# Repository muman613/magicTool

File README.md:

# magicTool

`magicTool` is a Raspberry Pi Pico 2 / Pico 2 W helper project used to drive debug GPIO over a simple USB serial command interface. It is intended as a standalone debug aid for other hardware and firmware work, including Argus-related debugging, but it is not part of the Argus project itself.

## Hardware Versions

The firmware supports two magicTool hardware version values:

- Hardware v1 is the basic configuration. It provides the USB serial command interface, D0-D3 GPIO outputs, and D0-D1 GPIO inputs without the display stack.
- Hardware v2 adds support for a 128x128 LCD display. Display-enabled builds compile the ST7735 driver, LVGL UI, and display task so the onboard screen can mirror the D0-D3 output states.

Select the target hardware with `MAGICTOOL_HW_VERSION`: use `1` for hardware v1 and `2` for hardware v2.

## Repository Layout

This repository is organized so the current Pico firmware lives in its own subdirectory and the project can grow without mixing host-side code, hardware assets, and embedded firmware sources.

```text
magicTool/
├── CMakeLists.txt
├── CMakePresets.json
├── docs/
│   ├── magiclib.md
│   ├── pico2w-build.md
│   └── pinout references
├── README.md
├── build.sh
├── firmware/
│   ├── CMakeLists.txt
│   ├── include/
│   ├── main.cpp
│   ├── src/
│   ├── reset_interface.c
│   ├── tusb_config.h
│   └── usb_descriptors.c
├── hardware/
│   ├── README.md
│   ├── generate_magictool_kicad.py
│   └── magictool.kicad_*
├── host/
│   ├── CMakeLists.txt
│   ├── README.md
│   ├── examples/
│   ├── include/
│   ├── src/
│   └── *.pc.in
├── resources/
│   ├── icons/
│   └── launchers/
├── magicTool_firmware.code-workspace
└── magicTool_host.code-workspace
```

- `firmware/` contains the Pico SDK and FreeRTOS based firmware build, plus optional LVGL display support for hardware v2.
- `host/` contains native POSIX and Qt5 libraries for talking to the Pico CDC serial device.
- `hardware/` contains the generated KiCad carrier board project and the script used to regenerate it.
- `docs/` contains project documentation, build notes, pinout references, and host library usage examples.
- `resources/` contains desktop integration assets for the host UI.

## Requirements

- `cmake` 3.16 or newer
- a native build tool supported by CMake such as `make` or `ninja`
- A working Raspberry Pi Pico SDK checkout
- `PICO_SDK_PATH` exported in your shell environment
- FreeRTOS-Kernel is fetched automatically for firmware builds when `FREERTOS_KERNEL_PATH` is not set
- Optionally, a Raspberry Pi FreeRTOS-Kernel checkout with `FREERTOS_KERNEL_PATH` exported in your shell environment, or a checkout at `/home/michael/gitroot/pico-dev/FreeRTOS-Kernel`
- An ARM embedded toolchain compatible with the Pico SDK
- LVGL is required only when building display-enabled firmware for hardware v2, which means `MAGICTOOL_HW_VERSION=2`. Set `LVGL_PATH` to a local checkout, clone LVGL under `firmware/external/lvgl`, or leave `MAGICTOOL_FETCH_LVGL=ON` to fetch it during configure.
- Qt5 Core and Qt5 SerialPort development packages for the Qt5 host library
- Qt5 Widgets development packages for the `magicUI` host application

The firmware presets require `PICO_SDK_PATH`. FreeRTOS-Kernel is fetched automatically unless `FREERTOS_KERNEL_PATH` points to an existing checkout:

```bash
export PICO_SDK_PATH=/path/to/pico-sdk
# Optional:
export FREERTOS_KERNEL_PATH=/path/to/FreeRTOS-Kernel
```

The host-only presets do not require the Pico SDK or FreeRTOS.

## Build

Prefer the CMake presets below. They keep host and firmware outputs in separate
build directories and avoid mixing the host toolchain with the Pico cross-toolchain.

For a concise Pico 2 W build matrix covering hardware v1 and v2, see
[docs/pico2w-build.md](docs/pico2w-build.md).

For the common cases, use the helper script:

```bash
./build.sh [pico2|pico2w] [host|fw|all] [1|2] [debug|release]
```

All arguments are optional. The defaults are `pico2`, `all`, hardware version
`1`, and `debug`:

```bash
./build.sh
```

Examples:

```bash
./build.sh pico2w fw 2 release
./build.sh pico2 host 1 debug
```

### Host Applications

The host build produces:

- `magictool`, the command-line example from `host/examples/basic_usage.cpp`
- `magictool_native`, the native command-line example from `host/examples/basic_usage_native.cpp`
- `magicUI`, the Qt Widgets application
- `libmagictool_native.a`, the native POSIX host library
- `libmagictool_qt5.a`, the Qt5 host library

Build host Debug:

```bash
cmake --preset host-debug
cmake --build --preset host-debug
```

Build host Release:

```bash
cmake --preset host-release
cmake --build --preset host-release
```

Build the native POSIX host library and `magictool_native` without Qt:

```bash
cmake -S host -B build/host-native-only \
  -DDEBUG_TOOL_BUILD_QT5=OFF \
  -DDEBUG_TOOL_BUILD_NATIVE=ON \
  -DDEBUG_TOOL_NATIVE_BUILD_EXAMPLES=ON
cmake --build build/host-native-only
```

Host output paths:

```text
build/host-debug/host/magictool
build/host-debug/host/magictool_native
build/host-debug/host/magicUI
build/host-debug/host/libmagictool_native.a
build/host-debug/host/libmagictool_qt5.a
build/host-release/host/magictool
build/host-release/host/magictool_native
build/host-release/host/magicUI
build/host-release/host/libmagictool_native.a
build/host-release/host/libmagictool_qt5.a
```

### Firmware Only

The default firmware hardware version is `MAGICTOOL_HW_VERSION=1`, which targets hardware v1 and builds the FreeRTOS USB/GPIO firmware without the display stack. Set `MAGICTOOL_HW_VERSION=2` to target hardware v2 and enable 128x128 ST7735/LVGL display support.

Build Pico 2 Debug:

```bash
cmake --preset firmware-pico2-debug
cmake --build --preset firmware-pico2-debug
```

Build Pico 2 Release:

```bash
cmake --preset firmware-pico2-release
cmake --build --preset firmware-pico2-release
```

Build Pico 2 W Debug:

```bash
cmake --preset firmware-pico2w-debug
cmake --build --preset firmware-pico2w-debug
```

Build Pico 2 W Release:

```bash
cmake --preset firmware-pico2w-release
cmake --build --preset firmware-pico2w-release
```

Firmware UF2 output paths:

```text
build/firmware-pico2-debug/firmware/magictool_fw_pico2.uf2
build/firmware-pico2-release/firmware/magictool_fw_pico2.uf2
build/firmware-pico2w-debug/firmware/magictool_fw_pico2_w.uf2
build/firmware-pico2w-release/firmware/magictool_fw_pico2_w.uf2
```

Build a display-enabled Pico 2 firmware manually by selecting hardware v2 and providing LVGL if you do not want CMake to fetch it:

```bash
cmake -S . -B build/firmware-pico2-hw2-release \
  -DCMAKE_BUILD_TYPE=Release \
  -DDEBUG_TOOL_BUILD_FIRMWARE=ON \
  -DDEBUG_TOOL_BUILD_HOST=OFF \
  -DMAGICTOOL_HW_VERSION=2 \
  -DLVGL_PATH=/path/to/lvgl
cmake --build build/firmware-pico2-hw2-release
```

### Host And Firmware Together

The combined presets build the selected firmware target and the host
applications in separate sub-builds under one top-level build directory.

Build all targets for Pico 2 Debug:

```bash
cmake --preset all-pico2-debug
cmake --build --preset all-pico2-debug
```

Build all targets for Pico 2 Release:

```bash
cmake --preset all-pico2-release
cmake --build --preset all-pico2-release
```

Build all targets for Pico 2 W Debug:

```bash
cmake --preset all-pico2w-debug
cmake --build --preset all-pico2w-debug
```

Build all targets for Pico 2 W Release:

```bash
cmake --preset all-pico2w-release
cmake --build --preset all-pico2w-release
```

Combined build output paths use nested sub-build directories:

```text
build/all-pico2-release/firmware/magictool_fw_pico2.uf2
build/all-pico2-release/host/magictool
build/all-pico2-release/host/magictool_native
build/all-pico2-release/host/magicUI
build/all-pico2w-release/firmware/magictool_fw_pico2_w.uf2
build/all-pico2w-release/host/magictool
build/all-pico2w-release/host/magictool_native
build/all-pico2w-release/host/magicUI
```

### Install Host Examples And Dev Artifacts

The host install includes two groups of files:

- host examples: runnable tools installed under `<prefix>/bin`
- development artifacts: static libraries, public headers, and `pkg-config`
  files used by other projects

The repository presets enable both Qt5 and native host examples, so a preset
host build installs the examples and development artifacts together. The
default install prefix is `/opt/magictool`.

Build and install the Release host preset:

```bash
cmake --preset host-release
cmake --build --preset host-release
cmake --install build/host-release
```

If the prefix requires elevated permissions:

```bash
sudo cmake --install build/host-release
```

To install into a user-writable prefix, set the prefix when configuring:

```bash
cmake --preset host-release -DCMAKE_INSTALL_PREFIX="$HOME/.local/magictool"
cmake --build --preset host-release
cmake --install build/host-release
```

The installed host examples are:

```text
<prefix>/bin/magictool
<prefix>/bin/magictool_native
<prefix>/bin/magicUI
```

The files under `bin/` are the installed host examples:

- `magictool` is the Qt5 command-line example from
  `host/examples/basic_usage.cpp`
- `magictool_native` is the native POSIX command-line example from
  `host/examples/basic_usage_native.cpp`
- `magicUI` is the Qt Widgets example application from
  `host/examples/magicUI.cpp`

The remaining files are the development artifacts needed to link another
project against magicTool:

```text
<prefix>/lib/libmagictool_native.a
<prefix>/lib/libmagictool_qt5.a
<prefix>/lib/pkgconfig/magictool_native.pc
<prefix>/lib/pkgconfig/magictool_qt5.pc
<prefix>/inc/magictool/magicdebug.h
<prefix>/inc/magictool/native/magicdebug.h
```

Combined builds install the host sub-build:

```bash
cmake --install build/all-pico2-release
```

If you configure the `host/` directory directly instead of using repository
presets, examples are optional. Enable them before installing:

```bash
cmake -S host -B build/host \
  -DDEBUG_TOOL_QT5_BUILD_EXAMPLES=ON \
  -DDEBUG_TOOL_NATIVE_BUILD_EXAMPLES=ON
cmake --build build/host
cmake --install build/host
```

For a native-only install without Qt, build only the native library and native
example:

```bash
cmake -S host -B build/host-native-only \
  -DDEBUG_TOOL_BUILD_QT5=OFF \
  -DDEBUG_TOOL_BUILD_NATIVE=ON \
  -DDEBUG_TOOL_NATIVE_BUILD_EXAMPLES=ON
cmake --build build/host-native-only
cmake --install build/host-native-only
```

## CI And Releases

GitHub Actions builds the host applications and Pico firmware on pull requests
and pushes to `main`.

Release builds run when a tag matching `v*` is pushed, or when the release
workflow is started manually from GitHub Actions. Tag releases publish these
artifacts to the GitHub release:

- `magictool-linux-x86_64.tar.gz`, containing the installed Linux host tools,
  static libraries, pkg-config files, and public headers
- `magictool_fw_pico2.uf2`
- `magictool_fw_pico2_w.uf2`

Create a release by tagging the commit and pushing the tag:

```bash
git tag v0.2.0
git push origin v0.2.0
```

### Manual CMake Options

Presets are wrappers around these root CMake options:

```text
DEBUG_TOOL_BUILD_HOST=ON|OFF
DEBUG_TOOL_BUILD_FIRMWARE=ON|OFF
DEBUG_TOOL_QT5_BUILD_EXAMPLES=ON|OFF
DEBUG_TOOL_NATIVE_BUILD_EXAMPLES=ON|OFF
PICO_2_W=ON|OFF
MAGICTOOL_HW_VERSION=1|2
MAGICTOOL_FW_VERSION_MAJOR=0
MAGICTOOL_FW_VERSION_MINOR=2
MAGICTOOL_FW_VERSION_REVISION=0
FREERTOS_KERNEL_PATH=/path/to/FreeRTOS-Kernel
MAGICTOOL_FETCH_FREERTOS=ON|OFF
FREERTOS_KERNEL_GIT_TAG=4f7299d6ea746b27a9dd19e87af568e34bd65b15
LVGL_PATH=/path/to/lvgl
MAGICTOOL_FETCH_LVGL=ON|OFF
LVGL_GIT_TAG=latest|vX.Y.Z
CMAKE_BUILD_TYPE=Debug|Release
```

FreeRTOS support uses the Raspberry Pi FreeRTOS-Kernel fork because the firmware needs its RP2350 ARM non-secure port. Set `FREERTOS_KERNEL_PATH` to use a local checkout, or leave `MAGICTOOL_FETCH_FREERTOS=ON` to fetch the commit selected by `FREERTOS_KERNEL_GIT_TAG`.

Display support is controlled by `MAGICTOOL_HW_VERSION`: hardware version `1` targets hardware v1 and does not compile or link LVGL/display code; hardware version `2` targets hardware v2 and compiles the ST7735 driver, LVGL UI, and display task. `LVGL_PATH`, `MAGICTOOL_FETCH_LVGL`, and `LVGL_GIT_TAG` are used only for display-enabled firmware.

For example, a manual host Release build is:

```bash
cmake -S . -B build/manual-host-release \
  -DCMAKE_BUILD_TYPE=Release \
  -DDEBUG_TOOL_BUILD_FIRMWARE=OFF \
  -DDEBUG_TOOL_BUILD_HOST=ON \
  -DDEBUG_TOOL_QT5_BUILD_EXAMPLES=ON \
  -DDEBUG_TOOL_NATIVE_BUILD_EXAMPLES=ON
cmake --build build/manual-host-release
```

The direct `host/` build also accepts these host-specific options:

```text
DEBUG_TOOL_BUILD_QT5=ON|OFF
DEBUG_TOOL_BUILD_NATIVE=ON|OFF
```

A manual Pico 2 W firmware Release build is:

```bash
cmake -S . -B build/manual-firmware-pico2w-release \
  -DCMAKE_BUILD_TYPE=Release \
  -DDEBUG_TOOL_BUILD_FIRMWARE=ON \
  -DDEBUG_TOOL_BUILD_HOST=OFF \
  -DPICO_2_W=ON
cmake --build build/manual-firmware-pico2w-release
```

To remove generated build output:

```bash
rm -rf build
```

For VS Code with CMake Tools, open one of these workspace files:

- `magicTool_host.code-workspace`
- `magicTool_firmware.code-workspace`

## Firmware Behavior

The firmware runs on FreeRTOS and exposes a USB CDC interface with a compact 2-byte binary protocol.

- Outputs `0..3` are mapped to GPIO `2, 3, 4, 5`
- Inputs `0..1` are mapped to GPIO `6, 7`
- The USB CDC task handles TinyUSB command receive and event transmit
- The protocol task applies GPIO commands and polls input-change notifications
- A zero-endpoint vendor reset interface is also exposed so `picotool` can force the device into BOOTSEL mode without pressing the BOOTSEL button
- Host command packets are 2 bytes: upper nibble = command, lower nibble = selector, second byte = argument
- Firmware replies are 2-byte event packets and may also include asynchronous input-change notifications
- Firmware versions use three bytes: major, minor, revision. `GET_VERSION` selector `0` returns major, selector `1` returns minor, and selector `2` returns revision.
- Hardware v2 adds a 128x128 display task. The display shows the firmware version and four centered virtual LEDs labeled D0-D3. The virtual LEDs mirror output GPIO states for D0-D3.

The current firmware supports output control, input/output bitmap reads, notification enable/disable, firmware version query, hardware version query, and ping.

Because the runtime firmware uses the custom USB VID/PID `0xcafe:0x4000`, force flashing with `picotool` should include that filter:

```bash
picotool load -f --vid 0xcafe --pid 0x4000 firmware/build_pico2/magictool_fw_pico2.uf2
```

## Host Libraries

The host-side native CMake target is `magictool_native_lib`, and the built library file is `libmagictool_native.a`. It uses the C++ standard library plus POSIX serial calls.

The host-side Qt5 CMake target is `magictool_qt5_lib`, and the built library file is `libmagictool_qt5.a`. It wraps `QSerialPort` and exposes a small synchronous API for talking to the firmware over the CDC serial interface.

Qt5 public header:

```text
host/include/magictool/magicdebug.h
```

Native public header:

```text
host/include/magictool/native/magicdebug.h
```

Key methods:

- `Open(const QString &portName)`
- `Pulse(quint8 outputIndex, quint8 count = 1)`
- `Set(quint8 outputIndex)`
- `Clear(quint8 outputIndex)`
- `Toggle(quint8 outputIndex)`
- `ReadInputs(quint8 *bitsOut = nullptr)`
- `ReadOutputs(quint8 *bitsOut = nullptr)`
- `GetVersion(quint8 *versionOut = nullptr)`
- `GetFirmwareVersion(Version *versionOut = nullptr)`
- `GetHardwareVersion(quint8 *hardwareVersionOut = nullptr)`
- `Ping(quint8 value, quint8 *echoedOut = nullptr)`
- `OpenTool()`
- `CloseTool()`
- `LastResponse()`
- `LastErrorString()`

`Open()` queries the firmware version and requires firmware major/minor to match the library major/minor. Revision is ignored for compatibility. `GetVersion()` is retained as a single-byte compatibility helper for the firmware major version; new code should use `GetFirmwareVersion()`.

Library documentation:

- `host/README.md`
- `docs/magiclib.md`

Quick example:

```cpp
#include <magictool/magicdebug.h>

magictool::DebugToolDevice device;
if (!device.Open("/dev/ttyACM0")) {
    qWarning() << device.LastErrorString();
    return;
}

if (!device.Pulse(0, 5)) {
    qWarning() << device.LastErrorString();
}
```

A buildable CLI example is also provided at `host/examples/basic_usage.cpp`.

## Simple magiclib App

After installing magicTool, another CMake project can link against the native
magiclib with `pkg-config`. This example opens the Pico serial device, sends one
ping, pulses output `0` five times, and prints the firmware response text.

Example layout:

```text
my_magic_app/
├── CMakeLists.txt
└── main.cpp
```

`main.cpp`:

```cpp
#include <cstdint>
#include <iostream>
#include <string>

#include <magictool/native/magicdebug.h>

int main(int argc, char **argv) {
    const std::string port = argc > 1 ? argv[1] : "/dev/ttyACM0";

    magictool::native::DebugToolDevice device;
    if (!device.Open(port)) {
        std::cerr << "Open failed: " << device.LastErrorString() << '\n';
        return 1;
    }

    std::uint8_t echoed = 0;
    if (!device.Ping(42, &echoed)) {
        std::cerr << "Ping failed: " << device.LastErrorString() << '\n';
        return 1;
    }

    if (!device.Pulse(0, 5)) {
        std::cerr << "Pulse failed: " << device.LastErrorString() << '\n';
        return 1;
    }

    std::cout << "Ping echoed " << static_cast<int>(echoed) << '\n';
    std::cout << "Last response: " << device.LastResponse() << '\n';
    return 0;
}
```

`CMakeLists.txt`:

```cmake
cmake_minimum_required(VERSION 3.16)

project(my_magic_app LANGUAGES CXX)

set(CMAKE_CXX_STANDARD 17)
set(CMAKE_CXX_STANDARD_REQUIRED ON)
set(CMAKE_CXX_EXTENSIONS OFF)

find_package(PkgConfig REQUIRED)
pkg_check_modules(MAGICTOOL_NATIVE REQUIRED IMPORTED_TARGET magictool_native)

add_executable(my_magic_app main.cpp)
target_link_libraries(my_magic_app PRIVATE PkgConfig::MAGICTOOL_NATIVE)
```

Build and run:

```bash
cmake -S . -B build
cmake --build build
./build/my_magic_app /dev/ttyACM0
```

If magicTool was installed into a non-standard prefix, point `pkg-config` at the
installed `.pc` file before configuring the app:

```bash
export PKG_CONFIG_PATH=/opt/magictool/lib/pkgconfig:$PKG_CONFIG_PATH
```

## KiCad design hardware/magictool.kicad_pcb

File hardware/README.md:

# magicTool KiCad hardware

This directory contains a generated KiCad 10 project for a small Raspberry Pi Pico 2 W carrier board matching the firmware pin map.

## Electrical interface

- `A1`: Raspberry Pi Pico 2 W module, using KiCad's Pico W SMD hand-solder footprint.
- `J1`: 8-pin 2.54 mm debug I/O header.
- `J1.1..J1.4`: `OUT0..OUT3`, mapped to Pico GPIO `2..5`.
- `J1.5..J1.6`: `IN0..IN1`, mapped directly to Pico GPIO `6..7`.
- `J1.7`: Pico `+3V3` output for low-current external references only.
- `J1.8`: `GND`.
- Inputs use the firmware's internal pulldowns.
- `J2`: RUN-to-GND reset header.

See the [magicTool J1 pinout SVG](../docs/magictool-pinout.svg) for a visual reference.

The board assumes USB power and USB data come from the Pico module's onboard connector.

## Regeneration

Run this from the repository root:

```bash
python3 hardware/generate_magictool_kicad.py
```

Then refill zones and run KiCad DRC:

```bash
kicad-cli pcb drc --refill-zones --save-board hardware/magictool.kicad_pcb
```

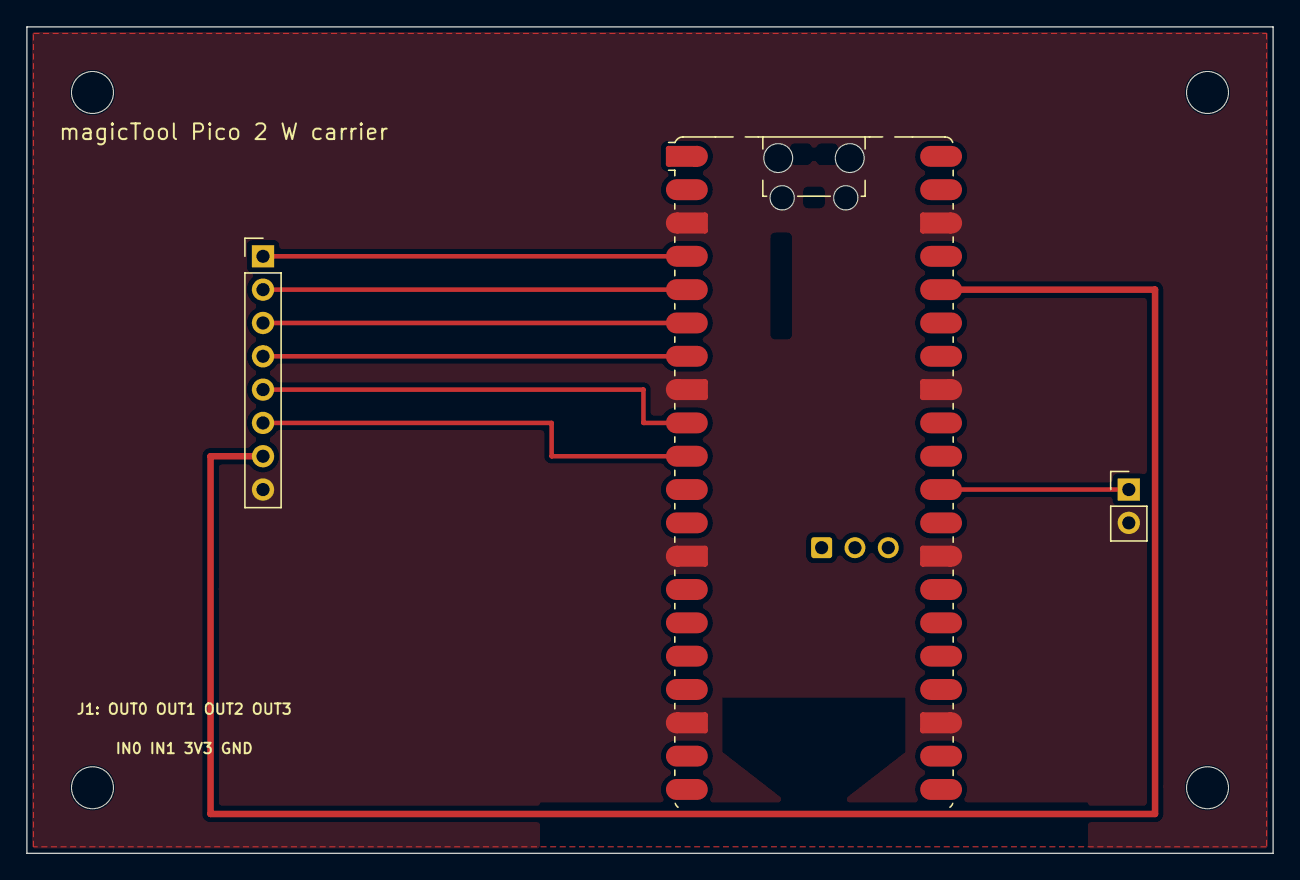
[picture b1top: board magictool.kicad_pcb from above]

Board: 2 copper layers, 95.0 x 63.0 mm, 7 parts (0 on the bottom side), 9 nets.

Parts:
A1: Raspberry Pi Pico 2 W; RaspberryPi_Pico_W_SMD_HandSolder
H1, H2, H3, H4: M3; MountingHole_3.2mm_M3
J1: magicTool I/O; PinHeader_1x08_P2.54mm_Vertical
J2: RUN; PinHeader_1x02_P2.54mm_Vertical

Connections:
+3V3: A1.36, J1.7
GND: A1.3, A1.8, A1.13, A1.18, A1.23, A1.28, A1.33, A1.38, J1.8, J2.2
IN0: A1.9, J1.5
IN1: A1.10, J1.6
OUT0: A1.4, J1.1
OUT1: A1.5, J1.2
OUT2: A1.6, J1.3
OUT3: A1.7, J1.4
RUN: A1.30, J2.1

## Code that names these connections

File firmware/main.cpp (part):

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static constexpr uint8_t HW_TYPE_PICO2 = 0x1;
static constexpr uint8_t HW_TYPE_PICO2_W = 0x2;

bi_decl(bi_4pins_with_names(2, "OUT0", 3, "OUT1", 4, "OUT2", 5, "OUT3"));
bi_decl(bi_2pins_with_names(6, "IN0 pulldown", 7, "IN1 pulldown"));
#if defined(PICO_DEFAULT_LED_PIN)
bi_decl(bi_1pin_with_name(PICO_DEFAULT_LED_PIN, "Indicator LED"));
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
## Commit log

2026-04-05 feat(firmware): enhance protocol and host library for improved I/O control
    This update includes major changes to both the Pico firmware and the Qt5 host library:
    1. **Firmware Enhancements:**
    - Transitioned USB interface from a serial command set to a 2-byte binary protocol.
    - Added support for specifying multiple outputs and inputs with synchronous API commands.
    - Introduced new commands: GET_VERSION, PING, WRITE_MASK, and ENABLE/DISABLE_NOTIFY.
    - Implemented a new input polling mechanism on a separate worker core for efficient event notifications.
2026-04-06 feat(debug_tool): enhance documentation and introduce GUI example
    This commit adds comprehensive project documentation under `docs/`, including usage examples for the host library. It introduces a new `magicUI` Qt5 Widgets example application, enhancing usability b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
2026-04-07 refactor(build): update CMake install paths and rename Qt5 library
    Added a default install prefix for host-side libraries to "/opt/magictool" with configuration options flexible through standard CMake cache variables. Updated CMakeLists.txt to include installation r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
    Renamed library files and namespaces from "debug_tool_qt5" to "magictool" to align with the project naming conventions. Updated the README and documentation files to reflect these changes, ensuring c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
2026-04-16 Add Pico 2 firmware target and LED control commands
    - Default firmware builds to Pico 2 with optional Pico 2 W support
    - Rename firmware target/output to magictool_fw variants
    - Add OPEN/CLOSE protocol commands for onboard indicator LED control
    - Expose OpenTool/CloseTool in the host library, CLI, and UI example
    - Document firmware build presets, Pico 2 W build steps, and new commands
    - Ignore firmware build artifacts
2026-04-16 feat(firmware): add hardware version query support
    Implemented functionality to query and report the hardware version alongside the firmware version. This involved adding a new command (`GET_HARDWARE_VERSION`) to the firmware, updating the host libra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
2026-04-17 feat(build): add support for Raspberry Pi Pico 2 W and new build presets
    This commit introduces an option to build firmware for the Raspberry Pi Pico 2 W (`PICO_2_W`) and expands the CMake preset configurations. New presets facilitate separate and combined builds for Pico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
2026-04-19 Add CI and release workflows
2026-04-19 feat(host): add native POSIX library support
    This commit introduces a native POSIX library (`magictool_native`) alongside the existing Qt5 library to enhance compatibility for host-side applications. Key changes include:
    - Addition of `magictool_native_lib` CMake target.
    - Support for building POSIX-based examples, including a new CLI example `magictool_native`.
    - Separate public headers and `pkg-config` files for native and Qt5 libraries.
    - Updated documentation to include usage and build instructions for both native and Qt5 libraries.
    These changes aim to make the host application compatible with environments that do not use Qt5, broadening usability across various platforms.
2026-04-19 chore(workflows): add libstdc++-arm-none-eabi-dev to CI and release jobs
    Added libstdc++-arm-none-eabi-dev to the package list in both ci.yml and release.yml workflows. This change ensures that the necessary C++ standard library for ARM is available during builds, which c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
2026-04-19 build(workflows): add newlib package to CI and release workflows
    Added libstdc++-arm-none-eabi-newlib to both CI and release GitHub workflows. This ensures compatibility with ARM-based development environments that rely on the newlib library, potentially fixing bu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
2026-04-19 chore(project): rename debug_tool to magicTool
    This commit updates the project name from `debug_tool` to `magicTool`. The changes include renaming the CMake project, options, and external project references, as well as updating file names and doc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
2026-04-19 feat(firmware): enhance version control and compatibility checks
    Introduce comprehensive firmware versioning comprising major, minor, and revision bytes. Implement new `GetFirmwareVersion()` for retrieving the full version and update relevant documentation and hos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
2026-04-19 feat(firmware): add USB reset interface for easy BOOTSEL mode activation
    This update introduces a zero-endpoint vendor reset interface to the firmware, enabling `picotool` to force the device into BOOTSEL mode without using the physical BOOTSEL button. The `.gitignore` fi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
    In the README, instructions are added for using the `picotool` with the custom USB VID/PID. The firmware build system and source files have been updated to integrate this new interface, enhancing eas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
2026-04-20 (doc): Better documentation of build and install
2026-04-20 feat(hardware): add initial KiCad project for Raspberry Pi Pico 2 W carrier
    Created a new KiCad 10 project directory for the Raspberry Pi Pico 2 W carrier board, including schematic and PCB layout files. Added script `generate_magictool_kicad.py` to automate project generati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
2026-04-23 refactor(hardware): streamline schematic wiring and update labels
    This commit enhances the Raspberry Pi Pico carrier schematic generation script by rerouting wires for improved readability, adjusting component positions for better alignment, and updating specific p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
2026-04-23 added pico pinouts
2026-05-13 docs: add pinout diagram for magicTool connections
    This commit adds a new SVG file, `magictool-pinout.svg`, which provides a visual reference for the connections between the magicTool J1 header and Raspberry Pi Pico 2. It includes detailed wiring fro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
2026-05-13 feat(firmware): add display support and update FreeRTOS integration
    Integrate LVGL display support for hardware revisions greater than v1, enabling an ST7735/LVGL status display. Updated the firmware to use FreeRTOS for task management, replacing previous queue handl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
    This update allows newer hardware versions to feature a display that mirrors GPIO output states, enhancing debug feedback without altering the host communication protocol.
2026-05-13 feat(build): enhance CI with versioned dependencies and build matrix
    Expanded the CI workflow to include a comprehensive hardware-specific build matrix for Pico 2 W, allowing both local and fetched dependency modes. Introduced automatic fetching of FreeRTOS and LVGL w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
2026-05-14 refactor(build): simplify CMake install command syntax
    Converted install command from a multi-line CODE block to a single line string for clarity and consistency with CMake syntax. This change reduces complexity and potential parsing errors associated wi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
2026-05-14 feat(build): add support for hardware version selection
    Added an optional hardware version argument to the build script, allowing users to specify either version 1 or 2. Updated README and usage instructions accordingly. This enhancement enables more prec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
2026-05-15 feat(display): enhance ST7735 display control and initialization
    Added new functions to improve the backlight and display management for the ST7735 screen. Introduced conditional compilation for C++ compatibility and adjusted the build process to use all available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
2026-05-15 Checkin readme
2026-05-15 feat(build): enhance installation for desktop integration
    Added new CMake configurations to support desktop integration of Magic Tool GUI application. This includes setting up install directories for resources, icons, and desktop application files. A .deskt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
2026-05-15 feat(magicUI): integrate resource file for window icon
    Added a Qt resource file (magicUI.qrc) and updated CMakeLists.txt to include the resource compilation with AUTORCC. Modified magicUI.cpp to set the application and main window icons using the newly a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
2026-05-15 feat(host): add JSON-based device configuration support
    This commit introduces JSON-based device configuration support, utilizing the nlohmann/json library. Key additions include the ability to specify named devices in a config file (`~/.config/magictool/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
    These enhancements aim to improve user workflow by managing device configurations centrally, reducing dependency on inconsistent `/dev/ttyACM*` paths by preferring sta
